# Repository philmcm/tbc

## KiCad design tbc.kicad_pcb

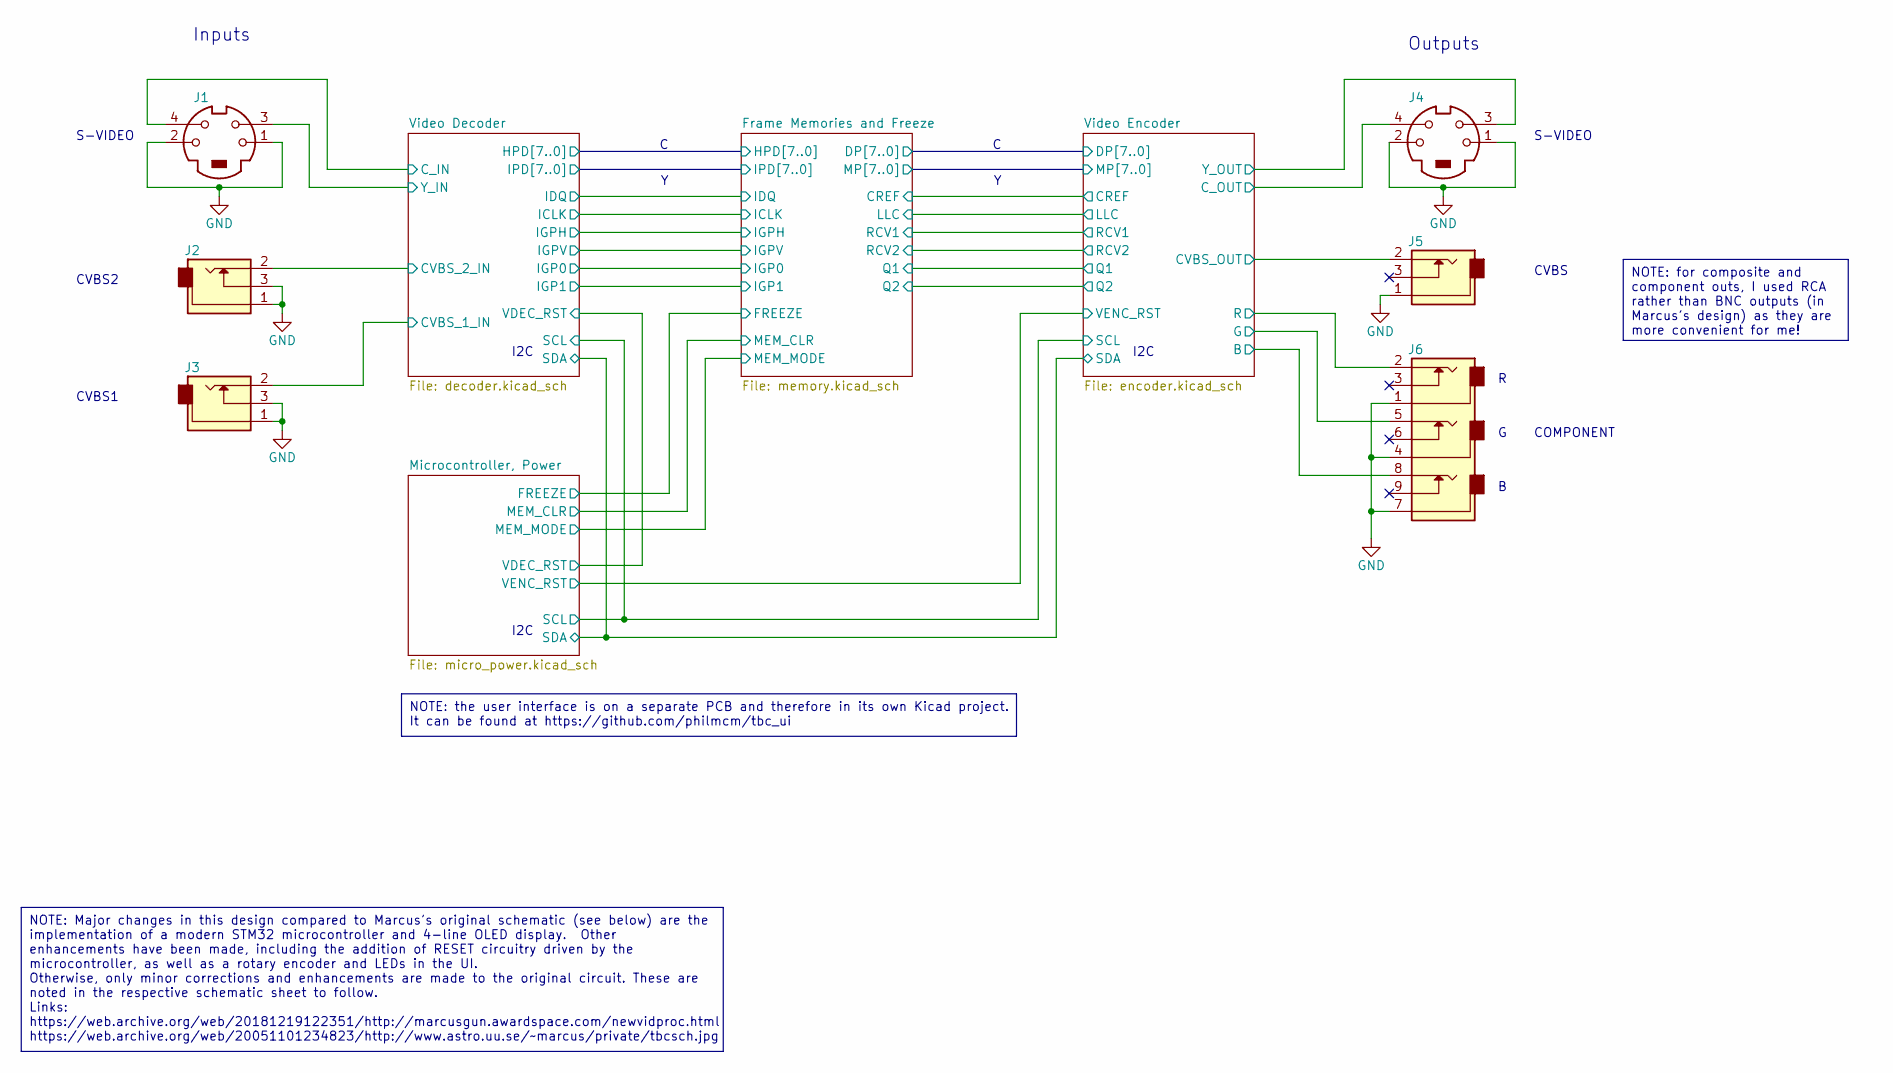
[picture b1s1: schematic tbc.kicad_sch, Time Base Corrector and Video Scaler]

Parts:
J1, J4: 5749181-1; Mouser 571-5749181-1
J2, J3, J5: PJRAN1X1U01X; Mouser 502-PJRAN1X1U01X
J6: PJRAN3X1U03X; Mouser 502-PJRAN3X1U03X

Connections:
/Video Decoder/CVBS_1_IN: J3.2; also elsewhere on the board
/Video Decoder/CVBS_2_IN: J2.2; also elsewhere on the board
/Video Decoder/C_IN: J1.4; also elsewhere on the board
/Video Decoder/Y_IN: J1.3; also elsewhere on the board
/Video Encoder/B: J6.8; also elsewhere on the board
/Video Encoder/CVBS_OUT: J5.2; also elsewhere on the board
/Video Encoder/C_OUT: J4.4; also elsewhere on the board
/Video Encoder/G: J6.5; also elsewhere on the board
/Video Encoder/R: J6.2; also elsewhere on the board
/Video Encoder/Y_OUT: J4.3; also elsewhere on the board
GND: J1.1, J1.2, J2.1, J2.3, J3.1, J3.3, J4.1, J4.2, J5.1, J6.1, J6.4, J6.7; also elsewhere on the board

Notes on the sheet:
NOTE: Major changes in this design compared to Marcus's original schematic (see below) are the implementation of a modern STM32 microcontroller and 4-line OLED display. Other enhancements have been made, including the addition of RESET circuitry driven by the microcontroller, as well as a rotary en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
NOTE: for composite and component outs, I used RCA rather than BNC outputs (in Marcus's design) as they are more convenient for me!
NOTE: the user interface is on a separate PCB and therefore in its own Kicad project. It can be found at https://github.com/philmcm/tbc_ui
Inputs
CVBS1
I2C
COMPONENT
CVBS
Outputs
CVBS2
S-VIDEO

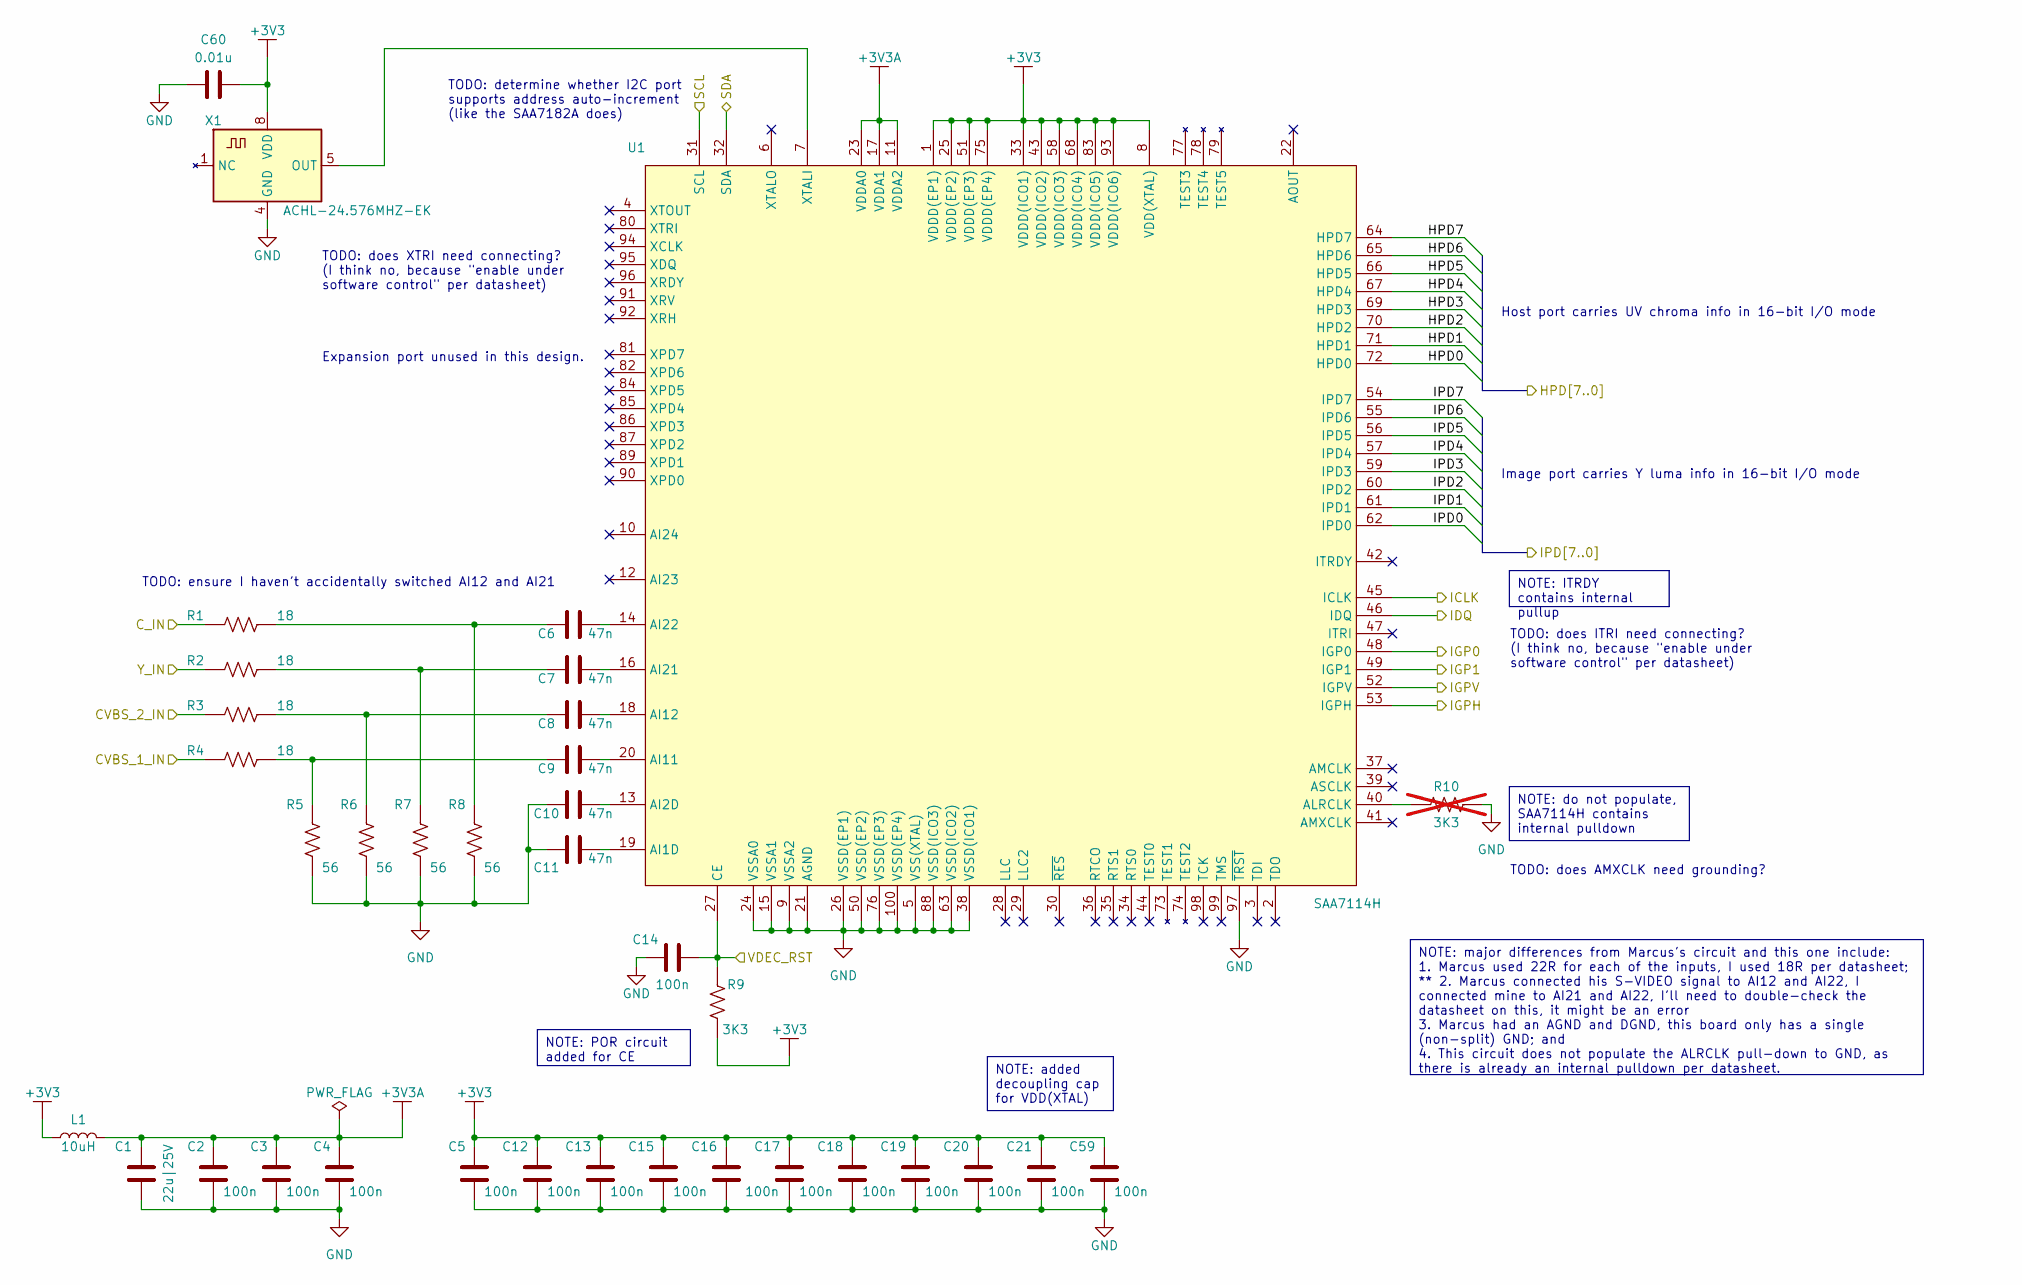
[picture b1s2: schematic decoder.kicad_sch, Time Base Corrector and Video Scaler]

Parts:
C1: 22u|25V; GRM32; Mouser 81-GRM32ER71E226KE5L
C2, C3, C4, C5, C12, C13, C14, C15, C16, C17, C18, C19, C20, C21, C59: 100n; C0603; Mouser 81-GCJ188R71H104KA2D
C6, C7, C8, C9, C10, C11: 47n; C0603; Mouser 81-GCJ188R71E473KA1D
C60: 0.01u; C0603; Mouser 81-GCM188R71H103KA7J
L1: 10uH; DFE201610E; Mouser 81-DFE201610E-100MP2
R1, R2, R3, R4: 18; R0603; Mouser 603-RC0603FR-0718RL
R5, R6, R7, R8: 56; R0603; Mouser 603-RC0603FR-0756RL
R9: 3K3; R0603; Mouser 603-RC0603FR-073K3L
R10: 3K3; R0603; Mouser 603-RC0603FR-073K3L; not fitted
U1: SAA7114H; LQFP100_14x14x1.4mm_Pitch0.5mm
X1: ACHL-24.576MHZ-EK; ACHL; Mouser 815-ACHL-24.576-EK

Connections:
+3V3: C5.2, C12.2, C13.2, C15.2, C16.2, C17.2, C18.2, C19.2, C20.2, C21.2, C59.2, C60.2, L1.1, R9.1, U1.1 (VDDD(EP1)), U1.8 (VDD(XTAL)), U1.25 (VDDD(EP2)), U1.33 (VDDD(ICO1)), U1.43 (VDDD(ICO2)), U1.51 (VDDD(EP3)), U1.58 (VDDD(ICO3)), U1.68 (VDDD(ICO4)), U1.75 (VDDD(EP4)), U1.83 (VDDD(ICO5)), U1.93 (VDDD(ICO6)), X1.8 (VDD); also elsewhere on the board
+3V3A: C1.2, C2.2, C3.2, C4.2, L1.2, U1.11 (VDDA2), U1.17 (VDDA1), U1.23 (VDDA0)
/Frame Memories and Freeze/HPD0: U1.72 (HPD0); also elsewhere on the board
/Frame Memories and Freeze/HPD1: U1.71 (HPD1); also elsewhere on the board
/Frame Memories and Freeze/HPD2: U1.70 (HPD2); also elsewhere on the board
/Frame Memories and Freeze/HPD3: U1.69 (HPD3); also elsewhere on the board
/Frame Memories and Freeze/HPD4: U1.67 (HPD4); also elsewhere on the board
/Frame Memories and Freeze/HPD5: U1.66 (HPD5); also elsewhere on the board
/Frame Memories and Freeze/HPD6: U1.65 (HPD6); also elsewhere on the board
/Frame Memories and Freeze/HPD7: U1.64 (HPD7); also elsewhere on the board
/Frame Memories and Freeze/ICLK: U1.45 (ICLK); also elsewhere on the board
/Frame Memories and Freeze/IDQ: U1.46 (IDQ); also elsewhere on the board
/Frame Memories and Freeze/IGP0: U1.48 (IGP0); also elsewhere on the board
/Frame Memories and Freeze/IGP1: U1.49 (IGP1); also elsewhere on the board
/Frame Memories and Freeze/IGPH: U1.53 (IGPH); also elsewhere on the board
/Frame Memories and Freeze/IGPV: U1.52 (IGPV); also elsewhere on the board
/Frame Memories and Freeze/IPD0: U1.62 (IPD0); also elsewhere on the board
/Frame Memories and Freeze/IPD1: U1.61 (IPD1); also elsewhere on the board
/Frame Memories and Freeze/IPD2: U1.60 (IPD2); also elsewhere on the board
/Frame Memories and Freeze/IPD3: U1.59 (IPD3); also elsewhere on the board
/Frame Memories and Freeze/IPD4: U1.57 (IPD4); also elsewhere on the board
/Frame Memories and Freeze/IPD5: U1.56 (IPD5); also elsewhere on the board
/Frame Memories and Freeze/IPD6: U1.55 (IPD6); also elsewhere on the board
/Frame Memories and Freeze/IPD7: U1.54 (IPD7); also elsewhere on the board
/Microcontroller, Power/SCL: U1.31 (SCL); also elsewhere on the board
/Microcontroller, Power/SDA: U1.32 (SDA); also elsewhere on the board
/Microcontroller, Power/VDEC_RST: C14.2, R9.2, U1.27 (CE); also elsewhere on the board
/Video Decoder/CVBS_1_IN: R4.1; also elsewhere on the board
/Video Decoder/CVBS_2_IN: R3.1; also elsewhere on the board
/Video Decoder/C_IN: R1.1; also elsewhere on the board
/Video Decoder/Y_IN: R2.1; also elsewhere on the board
GND: C1.1, C2.1, C3.1, C4.1, C5.1, C10.1, C11.1, C12.1, C13.1, C14.1, C15.1, C16.1, C17.1, C18.1, C19.1, C20.1, C21.1, C59.1, C60.1, R5.1, R6.1, R7.1, R8.1, R10.2, U1.5 (VSS(XTAL)), U1.9 (VSSA2), U1.15 (VSSA1), U1.21 (AGND), U1.24 (VSSA0), U1.26 (VSSD(EP1)), U1.38 (VSSD(ICO1)), U1.50 (VSSD(EP2)), U1.63 (VSSD(ICO2)), U1.76 (VSSD(EP3)), U1.88 (VSSD(ICO3)), U1.97 (~TRST), U1.100 (VSSD(EP4)), X1.4 (GND); also elsewhere on the board
unnamed: C6.1, R1.2, R8.2
unnamed: C7.1, R2.2, R7.2
unnamed: C8.1, R3.2, R6.2
unnamed: C9.1, R4.2, R5.2
unnamed: C11.2, U1.19 (AI1D)
unnamed: C10.2, U1.13 (AI2D)
unnamed: C9.2, U1.20 (AI11)
unnamed: C8.2, U1.18 (AI12)
unnamed: C7.2, U1.16 (AI21)
unnamed: C6.2, U1.14 (AI22)
unnamed: R10.1, U1.40 (ALRCLK)
unnamed: U1.7 (XTALI), X1.5 (OUT)

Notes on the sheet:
NOTE: ITRDY contains internal pullup
NOTE: do not populate, SAA7114H contains internal pulldown
NOTE: added decoupling cap for VDD(XTAL)
NOTE: POR circuit added for CE
NOTE: major differences from Marcus's circuit and this one include: 1. Marcus used 22R for each of the inputs, I used 18R per datasheet; ** 2. Marcus connected his S-VIDEO signal to AI12 and AI22, I connected mine to AI21 and AI22, I'll need to double-check the datasheet on this, it might be an err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
Image port carries Y luma info in 16-bit I/O mode
TODO: ensure I haven't accidentally switched AI12 and AI21
TODO: does AMXCLK need grounding?
Host port carries UV chroma info in 16-bit I/O mode
TODO: determine whether I2C port supports address auto-increment (like the SAA7182A does)
TODO: does ITRI need connecting? (I think no, because "enable under software control" per datasheet)
TODO: does XTRI need connecting? (I think no, because "enable under software control" per datasheet)
Expansion port unused in this design.

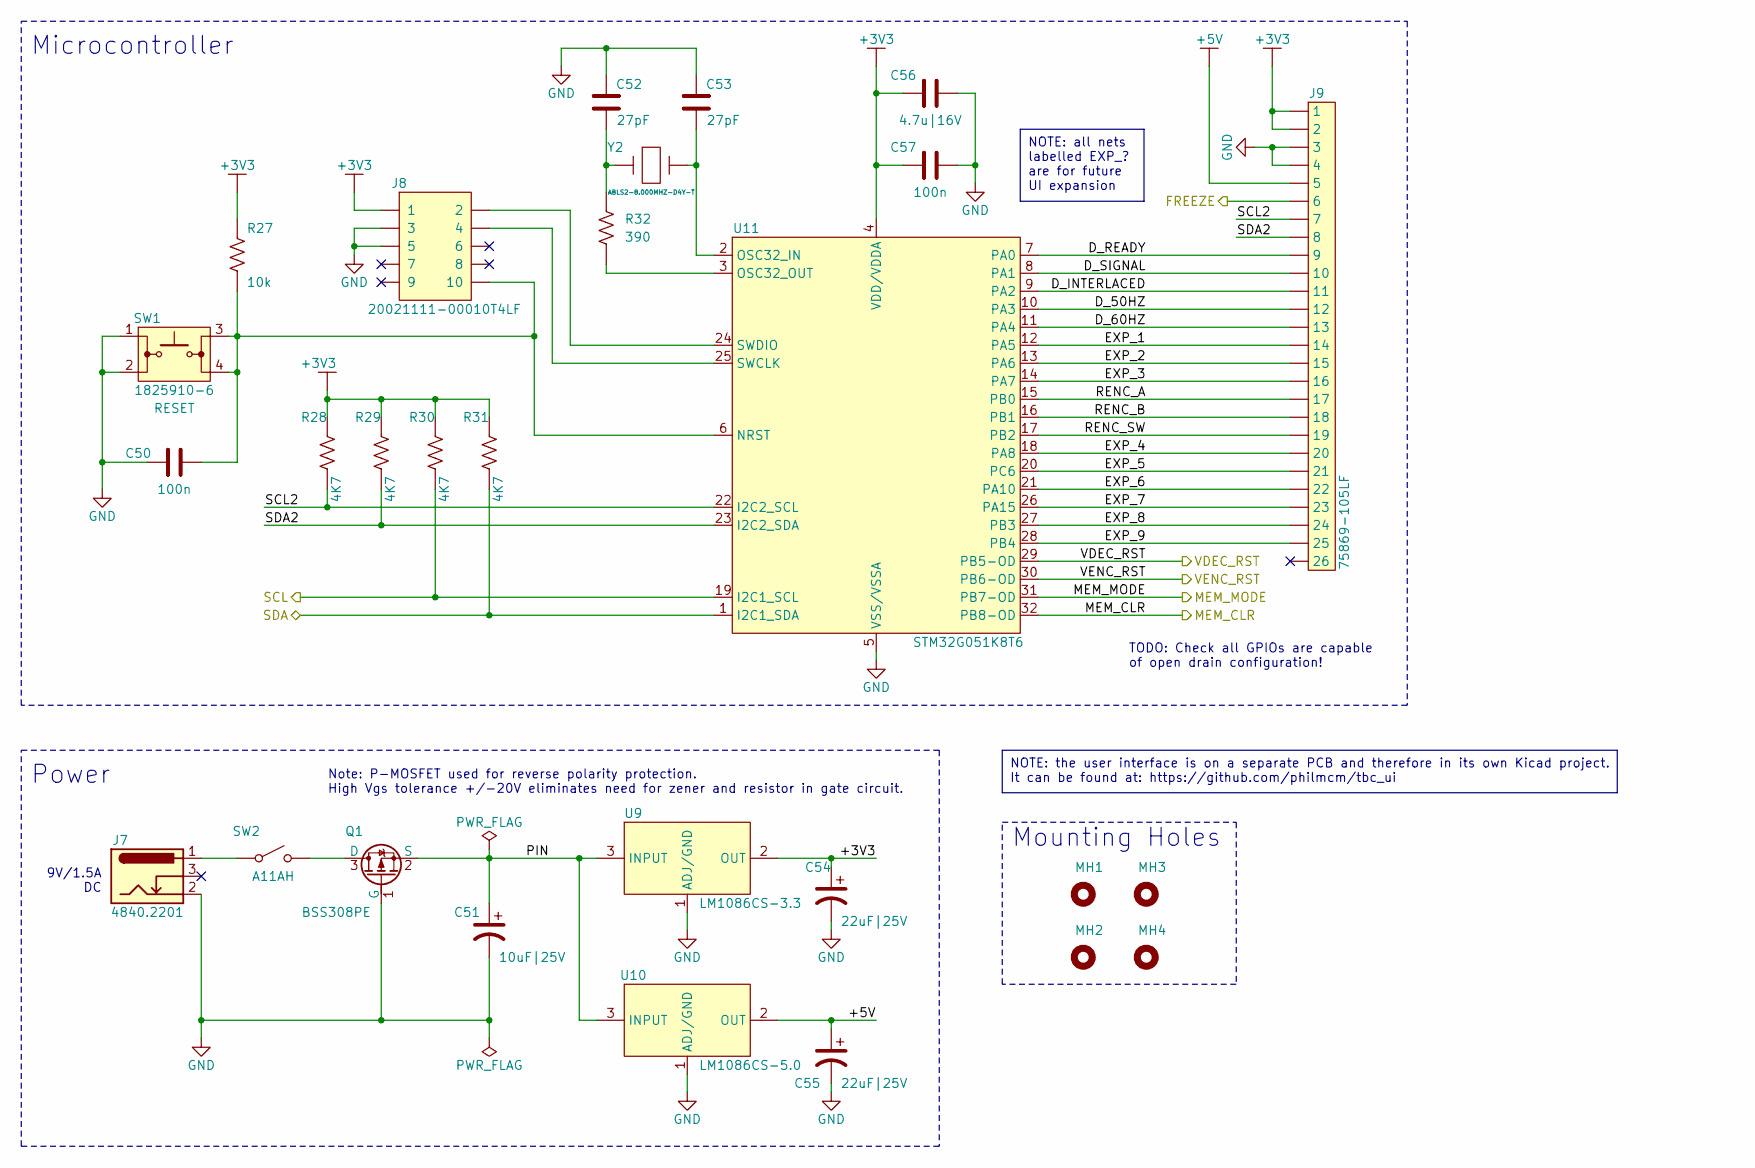
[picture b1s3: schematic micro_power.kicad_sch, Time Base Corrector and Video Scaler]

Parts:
C50, C57: 100n; C0603; Mouser 81-GCJ188R71H104KA2D
C51: 10uF|25V; 293D_C; Mouser 74-293D106X9025C2TE3
C52, C53: 27pF; C0603; Mouser 81-GCM1885C2A270JA6D
C54, C55: 22uF|25V; 593D_D; Mouser 74-593D226X9025D2TE3
C56: 4.7u|16V; C0603; Mouser 81-GRT188C71C475KE13
J7: 4840.2201; Mouser 693-4840.2201
J8: 20021111-00010T4LF; Digikey TC2030-IDC-ND
J9: 75869-105LF; Mouser 649-75869-105LF
MH1, MH2, MH3, MH4: MH_7.4MMNCx3.2MMD; MH_7.4MMCx3.2MMD_NON_COPPER_NPTH
Q1: BSS308PE; SOT23; Mouser 726-BSS308PEH6327XTS
R27: 10k; R0603; Mouser 603-RC0603FR-0710KL
R28, R29, R30, R31: 4K7; R0603; Mouser 603-RC0603FR-074K7L
R32: 390; R0603; Mouser 603-RC0603FR-07390RL
SW1: 1825910-6; Mouser 650-1825910-6
SW2: A11AH; Mouser 633-A11AH
U9: LM1086CS-3.3; TO-263_4.83mm; Mouser 926-LM1086CSX3.3NOPB
U10: LM1086CS-5.0; TO-263_4.83mm; Mouser 926-LM1086CS-5.0NOPB
U11: STM32G051K8T6; QFP32_7x7x1.6mm_Pitch0.8mm; Mouser 511-STM32G051K8T6
Y2: ABLS2-8.000MHZ-D4Y-T; ABLS2; Mouser 520-80-20-5PX-EM-TR

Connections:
+3V3: C54.1, C56.1, C57.1, J8.1, J9.1, J9.2, R27.2, R28.2, R29.2, R30.2, R31.2, U9.2 (OUT), U11.4 (VDD/VDDA); also elsewhere on the board
+5V: C55.1, J9.5, U10.2 (OUT); also elsewhere on the board
/Frame Memories and Freeze/FREEZE: J9.6; also elsewhere on the board
/Frame Memories and Freeze/MEM_CLR: U11.32 (PB8-OD); also elsewhere on the board
/Frame Memories and Freeze/MEM_MODE: U11.31 (PB7-OD); also elsewhere on the board
/Microcontroller, Power/D_50HZ: J9.12, U11.10 (PA3)
/Microcontroller, Power/D_60HZ: J9.13, U11.11 (PA4)
/Microcontroller, Power/D_INTERLACED: J9.11, U11.9 (PA2)
/Microcontroller, Power/D_READY: J9.9, U11.7 (PA0)
/Microcontroller, Power/D_SIGNAL: J9.10, U11.8 (PA1)
/Microcontroller, Power/EXP_1: J9.14, U11.12 (PA5)
/Microcontroller, Power/EXP_2: J9.15, U11.13 (PA6)
/Microcontroller, Power/EXP_3: J9.16, U11.14 (PA7)
/Microcontroller, Power/EXP_4: J9.20, U11.18 (PA8)
/Microcontroller, Power/EXP_5: J9.21, U11.20 (PC6)
/Microcontroller, Power/EXP_6: J9.22, U11.21 (PA10)
/Microcontroller, Power/EXP_7: J9.23, U11.26 (PA15)
/Microcontroller, Power/EXP_8: J9.24, U11.27 (PB3)
/Microcontroller, Power/EXP_9: J9.25, U11.28 (PB4)
/Microcontroller, Power/PIN: C51.1, Q1.2 (S), U9.3 (INPUT), U10.3 (INPUT)
/Microcontroller, Power/RENC_A: J9.17, U11.15 (PB0)
/Microcontroller, Power/RENC_B: J9.18, U11.16 (PB1)
/Microcontroller, Power/RENC_SW: J9.19, U11.17 (PB2)
/Microcontroller, Power/SCL: R30.1, U11.19 (I2C1_SCL); also elsewhere on the board
/Microcontroller, Power/SCL2: J9.7, R28.1, U11.22 (I2C2_SCL)
/Microcontroller, Power/SDA: R31.1, U11.1 (I2C1_SDA); also elsewhere on the board
/Microcontroller, Power/SDA2: J9.8, R29.1, U11.23 (I2C2_SDA)
/Microcontroller, Power/VDEC_RST: U11.29 (PB5-OD); also elsewhere on the board
/Microcontroller, Power/VENC_RST: U11.30 (PB6-OD); also elsewhere on the board
GND: C50.1, C51.2, C52.2, C53.2, C54.2, C55.2, C56.2, C57.2, J7.2, J8.3, J8.5, J9.3, J9.4, Q1.1 (G), SW1.1, SW1.2, U9.1 (ADJ/GND), U10.1 (ADJ/GND), U11.5 (VSS/VSSA); also elsewhere on the board
unnamed: C52.1, R32.2, Y2.1
unnamed: Q1.3 (D), SW2.3 (B)
unnamed: J7.1, SW2.1 (A)
unnamed: J8.2, U11.24 (SWDIO)
unnamed: J8.4, U11.25 (SWCLK)
unnamed: C53.1, U11.2 (OSC32_IN), Y2.2
unnamed: R32.1, U11.3 (OSC32_OUT)
unnamed: C50.2, J8.10, R27.1, SW1.3, SW1.4, U11.6 (NRST)

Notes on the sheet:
NOTE: the user interface is on a separate PCB and therefore in its own Kicad project. It can be found at: https://github.com/philmcm/tbc_ui
NOTE: all nets labelled EXP_? are for future UI expansion
Note: P-MOSFET used for reverse polarity protection. High Vgs tolerance +/-20V eliminates need for zener and resistor in gate circuit.
9V/1.5A DC
Mounting Holes
Microcontroller
TODO: Check all GPIOs are capable of open drain configuration!
Power

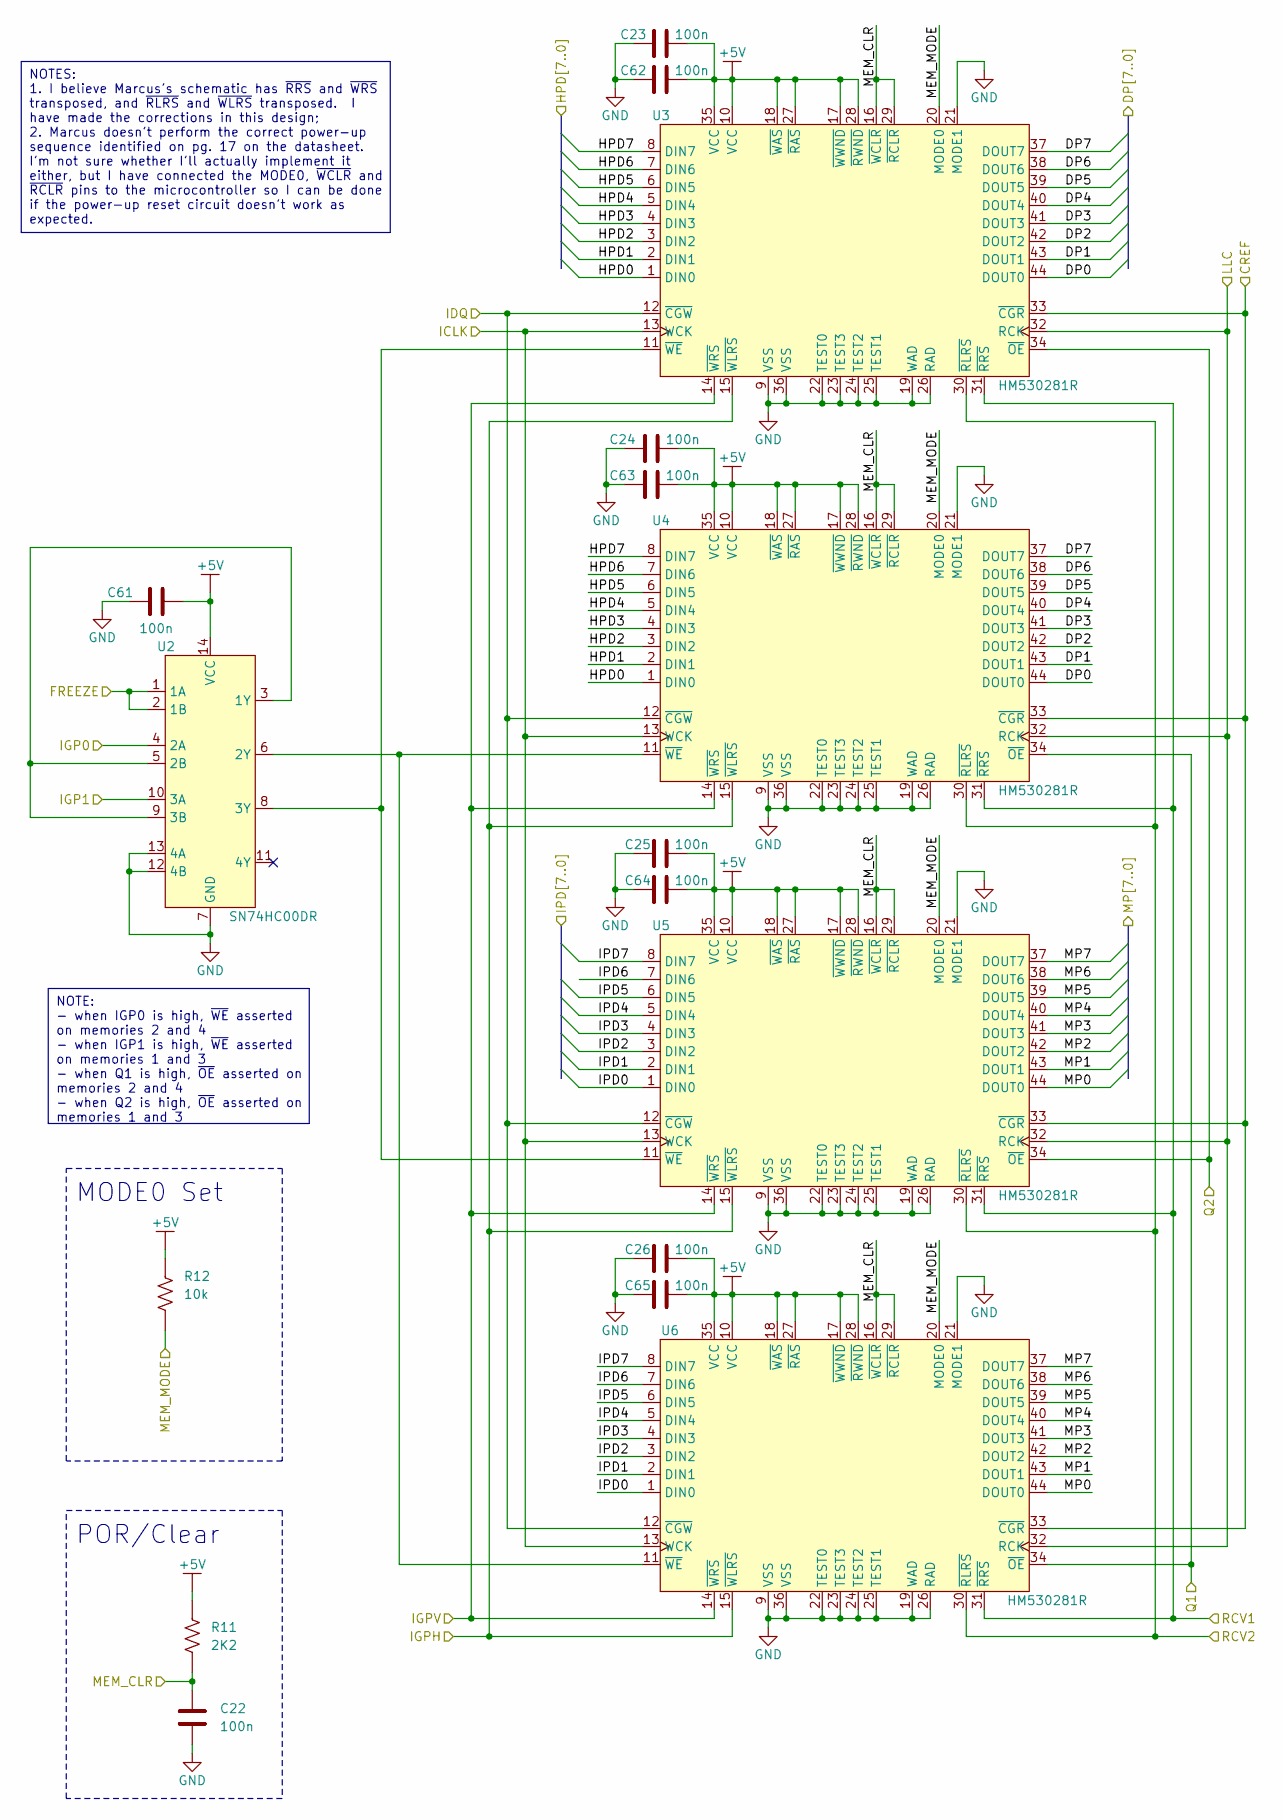
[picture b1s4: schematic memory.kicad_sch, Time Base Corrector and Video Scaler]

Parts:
C22, C23, C24, C25, C26, C61, C62, C63, C64, C65: 100n; C0603; Mouser 81-GCJ188R71H104KA2D
R11: 2K2; R0603; Mouser 603-RC0603FR-072K2L
R12: 10k; R0603; Mouser 603-RC0603FR-0710KL
U2: SN74HC00DR; SOIC-14; Mouser 595-SN74HC00DR
U3, U4, U5, U6: HM530281R; TTP-44DB

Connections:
+5V: C23.2, C24.2, C25.2, C26.2, C61.2, C62.2, C63.2, C64.2, C65.2, R11.2, R12.2, U2.14 (VCC), U3.10 (VCC), U3.17 (~WWND), U3.18 (~WAS), U3.27 (~RAS), U3.28 (~RWND), U3.35 (VCC), U4.10 (VCC), U4.17 (~WWND), U4.18 (~WAS), U4.27 (~RAS), U4.28 (~RWND), U4.35 (VCC), U5.10 (VCC), U5.17 (~WWND), U5.18 (~WAS), U5.27 (~RAS), U5.28 (~RWND), U5.35 (VCC), U6.10 (VCC), U6.17 (~WWND), U6.18 (~WAS), U6.27 (~RAS), U6.28 (~RWND), U6.35 (VCC); also elsewhere on the board
/Frame Memories and Freeze/CREF: U3.33 (~CGR), U4.33 (~CGR), U5.33 (~CGR), U6.33 (~CGR); also elsewhere on the board
/Frame Memories and Freeze/DP0: U3.44 (DOUT0), U4.44 (DOUT0); also elsewhere on the board
/Frame Memories and Freeze/DP1: U3.43 (DOUT1), U4.43 (DOUT1); also elsewhere on the board
/Frame Memories and Freeze/DP2: U3.42 (DOUT2), U4.42 (DOUT2); also elsewhere on the board
/Frame Memories and Freeze/DP3: U3.41 (DOUT3), U4.41 (DOUT3); also elsewhere on the board
/Frame Memories and Freeze/DP4: U3.40 (DOUT4), U4.40 (DOUT4); also elsewhere on the board
/Frame Memories and Freeze/DP5: U3.39 (DOUT5), U4.39 (DOUT5); also elsewhere on the board
/Frame Memories and Freeze/DP6: U3.38 (DOUT6), U4.38 (DOUT6); also elsewhere on the board
/Frame Memories and Freeze/DP7: U3.37 (DOUT7), U4.37 (DOUT7); also elsewhere on the board
/Frame Memories and Freeze/FREEZE: U2.1 (1A), U2.2 (1B); also elsewhere on the board
/Frame Memories and Freeze/HPD0: U3.1 (DIN0), U4.1 (DIN0); also elsewhere on the board
/Frame Memories and Freeze/HPD1: U3.2 (DIN1), U4.2 (DIN1); also elsewhere on the board
/Frame Memories and Freeze/HPD2: U3.3 (DIN2), U4.3 (DIN2); also elsewhere on the board
/Frame Memories and Freeze/HPD3: U3.4 (DIN3), U4.4 (DIN3); also elsewhere on the board
/Frame Memories and Freeze/HPD4: U3.5 (DIN4), U4.5 (DIN4); also elsewhere on the board
/Frame Memories and Freeze/HPD5: U3.6 (DIN5), U4.6 (DIN5); also elsewhere on the board
/Frame Memories and Freeze/HPD6: U3.7 (DIN6), U4.7 (DIN6); also elsewhere on the board
/Frame Memories and Freeze/HPD7: U3.8 (DIN7), U4.8 (DIN7); also elsewhere on the board
/Frame Memories and Freeze/ICLK: U3.13 (WCK), U4.13 (WCK), U5.13 (WCK), U6.13 (WCK); also elsewhere on the board
/Frame Memories and Freeze/IDQ: U3.12 (~CGW), U4.12 (~CGW), U5.12 (~CGW), U6.12 (~CGW); also elsewhere on the board
/Frame Memories and Freeze/IGP0: U2.4 (2A); also elsewhere on the board
/Frame Memories and Freeze/IGP1: U2.10 (3A); also elsewhere on the board
/Frame Memories and Freeze/IGPH: U3.15 (~WLRS), U4.15 (~WLRS), U5.15 (~WLRS), U6.15 (~WLRS); also elsewhere on the board
/Frame Memories and Freeze/IGPV: U3.14 (~WRS), U4.14 (~WRS), U5.14 (~WRS), U6.14 (~WRS); also elsewhere on the board
/Frame Memories and Freeze/IPD0: U5.1 (DIN0), U6.1 (DIN0); also elsewhere on the board
/Frame Memories and Freeze/IPD1: U5.2 (DIN1), U6.2 (DIN1); also elsewhere on the board
/Frame Memories and Freeze/IPD2: U5.3 (DIN2), U6.3 (DIN2); also elsewhere on the board
/Frame Memories and Freeze/IPD3: U5.4 (DIN3), U6.4 (DIN3); also elsewhere on the board
/Frame Memories and Freeze/IPD4: U5.5 (DIN4), U6.5 (DIN4); also elsewhere on the board
/Frame Memories and Freeze/IPD5: U5.6 (DIN5), U6.6 (DIN5); also elsewhere on the board
/Frame Memories and Freeze/IPD6: U5.7 (DIN6), U6.7 (DIN6); also elsewhere on the board
/Frame Memories and Freeze/IPD7: U5.8 (DIN7), U6.8 (DIN7); also elsewhere on the board
/Frame Memories and Freeze/LLC: U3.32 (RCK), U4.32 (RCK), U5.32 (RCK), U6.32 (RCK); also elsewhere on the board
/Frame Memories and Freeze/MEM_CLR: C22.2, R11.1, U3.16 (~WCLR), U3.29 (~RCLR), U4.16 (~WCLR), U4.29 (~RCLR), U5.16 (~WCLR), U5.29 (~RCLR), U6.16 (~WCLR), U6.29 (~RCLR); also elsewhere on the board
/Frame Memories and Freeze/MEM_MODE: R12.1, U3.20 (MODE0), U4.20 (MODE0), U5.20 (MODE0), U6.20 (MODE0); also elsewhere on the board
/Frame Memories and Freeze/MP0: U5.44 (DOUT0), U6.44 (DOUT0); also elsewhere on the board
/Frame Memories and Freeze/MP1: U5.43 (DOUT1), U6.43 (DOUT1); also elsewhere on the board
/Frame Memories and Freeze/MP2: U5.42 (DOUT2), U6.42 (DOUT2); also elsewhere on the board
/Frame Memories and Freeze/MP3: U5.41 (DOUT3), U6.41 (DOUT3); also elsewhere on the board
/Frame Memories and Freeze/MP4: U5.40 (DOUT4), U6.40 (DOUT4); also elsewhere on the board
/Frame Memories and Freeze/MP5: U5.39 (DOUT5), U6.39 (DOUT5); also elsewhere on the board
/Frame Memories and Freeze/MP6: U5.38 (DOUT6), U6.38 (DOUT6); also elsewhere on the board
/Frame Memories and Freeze/MP7: U5.37 (DOUT7), U6.37 (DOUT7); also elsewhere on the board
/Frame Memories and Freeze/Q1: U4.34 (~OE), U6.34 (~OE); also elsewhere on the board
/Frame Memories and Freeze/Q2: U3.34 (~OE), U5.34 (~OE); also elsewhere on the board
/Frame Memories and Freeze/RCV1: U3.31 (~RRS), U4.31 (~RRS), U5.31 (~RRS), U6.31 (~RRS); also elsewhere on the board
/Frame Memories and Freeze/RCV2: U3.30 (~RLRS), U4.30 (~RLRS), U5.30 (~RLRS), U6.30 (~RLRS); also elsewhere on the board
GND: C22.1, C23.1, C24.1, C25.1, C26.1, C61.1, C62.1, C63.1, C64.1, C65.1, U2.7 (GND), U2.12 (4B), U2.13 (4A), U3.9 (VSS), U3.19 (WAD), U3.21 (MODE1), U3.22 (TEST0), U3.23 (TEST3), U3.24 (TEST2), U3.25 (TEST1), U3.26 (RAD), U3.36 (VSS), U4.9 (VSS), U4.19 (WAD), U4.21 (MODE1), U4.22 (TEST0), U4.23 (TEST3), U4.24 (TEST2), U4.25 (TEST1), U4.26 (RAD), U4.36 (VSS), U5.9 (VSS), U5.19 (WAD), U5.21 (MODE1), U5.22 (TEST0), U5.23 (TEST3), U5.24 (TEST2), U5.25 (TEST1), U5.26 (RAD), U5.36 (VSS), U6.9 (VSS), U6.19 (WAD), U6.21 (MODE1), U6.22 (TEST0), U6.23 (TEST3), U6.24 (TEST2), U6.25 (TEST1), U6.26 (RAD), U6.36 (VSS); also elsewhere on the board
unnamed: U2.3 (1Y), U2.5 (2B), U2.9 (3B)
unnamed: U2.6 (2Y), U4.11 (~WE), U6.11 (~WE)
unnamed: U2.8 (3Y), U3.11 (~WE), U5.11 (~WE)

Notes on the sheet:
NOTE: - when IGP0 is high, ~{WE} asserted on memories 2 and 4 - when IGP1 is high, ~{WE} asserted on memories 1 and 3 - when Q1 is high, ~{OE} asserted on memories 2 and 4 - when Q2 is high, ~{OE} asserted on memories 1 and 3
NOTES: 1. I believe Marcus's schematic has ~{RRS} and ~{WRS} transposed, and ~{RLRS} and ~{WLRS} transposed. I have made the corrections in this design; 2. Marcus doesn't perform the correct power-up sequence identified on pg. 17 on the datasheet. I'm not sure whether I'll actually implement it eit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
MODE0 Set
POR/Clear

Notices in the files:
tbc.kicad_sch:
Enhancements © 2024 Phil McMillan
Original TBC circuit design © 2001 Marcus Gunnarsson (refer links on left)
